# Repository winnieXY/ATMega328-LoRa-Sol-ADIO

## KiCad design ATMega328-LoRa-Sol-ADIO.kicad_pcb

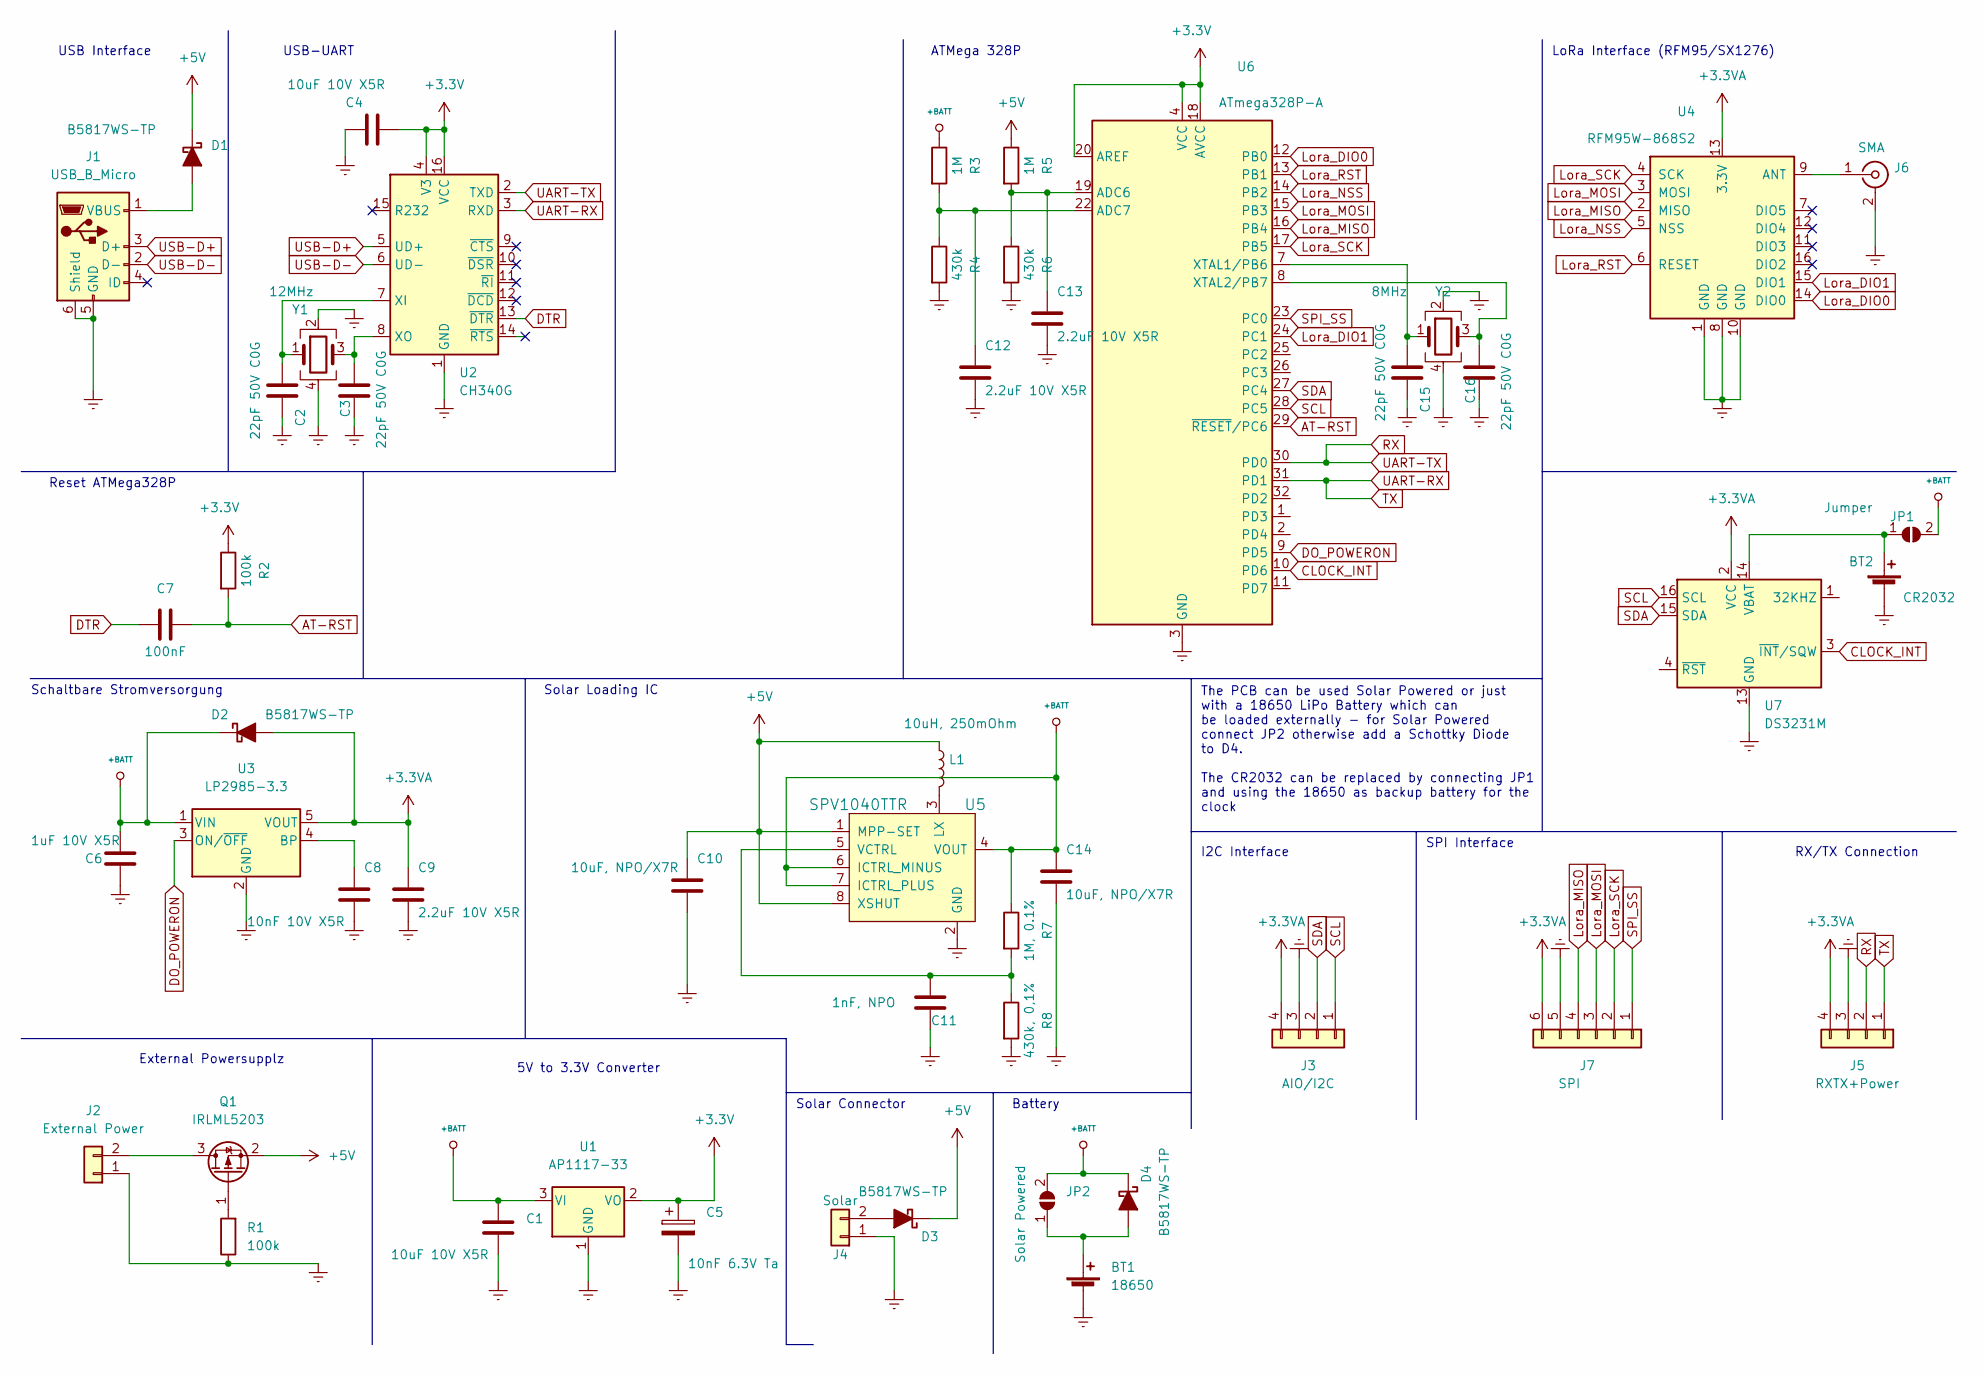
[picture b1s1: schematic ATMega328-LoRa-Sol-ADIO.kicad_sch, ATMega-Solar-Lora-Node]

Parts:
BT1: 18650; BatteryHolder_MPD_BH-18650-PC2
BT2: CR2032; Battery_Panasonic_CR2032-VS1N_Vertical_CircularHoles
C1, C4: 10uF 10V X5R; C_0603_1608Metric_Pad1.08x0.95mm_HandSolder; LCSC-Part C19702
C2, C3, C15, C16: 22pF 50V C0G; C_0603_1608Metric_Pad1.08x0.95mm_HandSolder; LCSC-Part C1653
C5: 10nF 6.3V Ta; CP_EIA-3528-15_AVX-H_Pad1.50x2.35mm_HandSolder; LCSC-Part C16133
C6: 1uF 10V X5R; C_0603_1608Metric_Pad1.08x0.95mm_HandSolder; LCSC-Part C19702
C7: 100nF; C_0603_1608Metric_Pad1.08x0.95mm_HandSolder; LCSC-Part C1653
C8: 10nF 10V X5R; C_0603_1608Metric_Pad1.08x0.95mm_HandSolder; LCSC-Part C19702
C9, C12, C13: 2.2uF 10V X5R; C_0603_1608Metric_Pad1.08x0.95mm_HandSolder; LCSC-Part C19702
C10, C14: 10uF, NPO/X7R; C_0603_1608Metric_Pad1.08x0.95mm_HandSolder; LCSC-Part C19702
C11: 1nF, NPO; C_0603_1608Metric_Pad1.08x0.95mm_HandSolder; LCSC-Part C19702
D1, D2, D3, D4: B5817WS-TP; D_SOD-323_HandSoldering; LCSC-Part C123899
J1: USB_B_Micro; USB_Micro-B_Molex-105017-0001
J2: External Power; JST_XH_B2B-XH-A_1x02_P2.50mm_Vertical
J3: AIO/I2C; JST_XH_B4B-XH-A_1x04_P2.50mm_Vertical
J4: Solar; JST_XH_B2B-XH-A_1x02_P2.50mm_Vertical
J5: RXTX+Power; JST_XH_B4B-XH-A_1x04_P2.50mm_Vertical
J6: SMA; SMA_Amphenol_901-144_Vertical
J7: SPI; JST_XH_B6B-XH-A_1x06_P2.50mm_Vertical
JP1: Jumper; SolderJumper-2_P1.3mm_Open_RoundedPad1.0x1.5mm
JP2: Solar Powered; SolderJumper-2_P1.3mm_Open_Pad1.0x1.5mm
L1: 10uH, 250mOhm; L_1206_3216Metric_Pad1.42x1.75mm_HandSolder
Q1: IRLML5203; SOT-23; LCSC-Part C2985623
R1: 100k; R_1206_3216Metric_Pad1.30x1.75mm_HandSolder; LCSC-Part C2907421
R2: 100k; R_1206_3216Metric_Pad1.30x1.75mm_HandSolder; LCSC-Part C17902
R3, R5: 1M; R_1206_3216Metric_Pad1.30x1.75mm_HandSolder; LCSC-Part C17902
R4, R6: 430k; R_1206_3216Metric_Pad1.30x1.75mm_HandSolder; LCSC-Part C17902
R7: 1M, 0.1%; R_1206_3216Metric_Pad1.30x1.75mm_HandSolder; LCSC-Part C17902
R8: 430k, 0,1%; R_1206_3216Metric_Pad1.30x1.75mm_HandSolder; LCSC-Part C17902
U1: AP1117-33; SOT-223-3_TabPin2; LCSC-Part C108785
U2: CH340G; SOIC-16_3.9x9.9mm_P1.27mm; LCSC-Part C14267
U3: LP2985-3.3; SOT-23-5
U4: RFM95W-868S2; HOPERF_RFM9XW_SMD; LCSC-Part C2844473
U5: SPV1040TTR; TSSOP-8_W4.4mm; MPN SPV1040TTR; Digi-Key_PN 497-11288-1-ND
U6: ATmega328P-A; TQFP-32_7x7mm_P0.8mm
U7: DS3231M; SOIC-16W_7.5x10.3mm_P1.27mm
Y1: 12MHz; Crystal_SMD_3225-4Pin_3.2x2.5mm_HandSoldering; LCSC-Part C9002
Y2: 8MHz; Crystal_SMD_3225-4Pin_3.2x2.5mm_HandSoldering; LCSC-Part C9002

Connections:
+3.3VA: C9.1, D2.2 (A), J3.4, J5.4, J7.6, U3.5 (VOUT), U4.13 (3.3V), U7.2 (VCC)
+3V3: C4.2, C5.1, R2.1, U1.2 (VO), U2.4 (V3), U2.16 (VCC), U6.4 (VCC), U6.6 (VCC), U6.18 (AVCC), U6.20 (AREF)
+5V: C10.1, D1.1 (K), D3.1 (K), L1.1, Q1.2 (S), R5.1, U5.1 (MPP-SET), U5.8 (XSHUT)
+BATT: C1.1, C6.1, C14.1, D2.1 (K), D4.1 (K), JP1.2 (B), JP2.2 (B), R3.1, R7.1, U1.3 (VI), U3.1 (VIN), U5.4 (VOUT), U5.6 (ICTRL_MINUS), U5.7 (ICTRL_PLUS)
AT-RST: C7.2, R2.2, U6.29 (~RESET/PC6)
CLOCK_INT: U6.10 (PD6), U7.3 (~INT/SQW)
DO_POWERON: U3.3 (ON/~OFF), U6.9 (PD5)
DTR: C7.1, U2.13 (~DTR)
Earth: BT1.2 (-), BT2.2 (-), C1.2, C2.2, C3.2, C4.1, C5.2, C6.2, C8.2, C9.2, C10.2, C11.2, C12.2, C13.2, C14.2, C15.2, C16.2, J1.5 (GND), J1.6 (Shield), J2.1, J3.3, J4.1, J5.3, J6.2 (Ext), J7.5, R1.1, R4.2, R6.2, R8.2, U1.1 (GND), U2.1 (GND), U3.2 (GND), U4.1 (GND), U4.8 (GND), U4.10 (GND), U5.2 (GND), U6.3 (GND), U6.5 (GND), U6.21 (GND), U7.5 (GND), U7.6 (GND), U7.7 (GND), U7.8 (GND), U7.9 (GND), U7.10 (GND), U7.11 (GND), U7.12 (GND), U7.13 (GND), Y1.2, Y1.4, Y2.2, Y2.4
Lora_DIO0: U4.14 (DIO0), U6.12 (PB0)
Lora_DIO1: U4.15 (DIO1), U6.24 (PC1)
Lora_MISO: J7.4, U4.2 (MISO), U6.16 (PB4)
Lora_MOSI: J7.3, U4.3 (MOSI), U6.15 (PB3)
Lora_NSS: U4.5 (NSS), U6.14 (PB2)
Lora_RST: U4.6 (RESET), U6.13 (PB1)
Lora_SCK: J7.2, U4.4 (SCK), U6.17 (PB5)
unnamed: BT1.1 (+), D4.2 (A), JP2.1 (A)
unnamed: BT2.1 (+), JP1.1 (A), U7.14 (VBAT)
unnamed: C2.1, U2.7 (XI), Y1.1
unnamed: C3.1, U2.8 (XO), Y1.3
unnamed: C8.1, U3.4 (BP)
unnamed: C11.1, R7.2, R8.1, U5.5 (VCTRL)
unnamed: C12.1, R3.2, R4.1, U6.22 (ADC7)
unnamed: C13.1, R5.2, R6.1, U6.19 (ADC6)
unnamed: C15.1, U6.7 (XTAL1/PB6), Y2.1
unnamed: C16.1, U6.8 (XTAL2/PB7), Y2.3
unnamed: D1.2 (A), J1.1 (VBUS)
unnamed: D3.2 (A), J4.2
unnamed: J2.2, Q1.3 (D)
unnamed: J6.1 (In), U4.9 (ANT)
unnamed: L1.2, U5.3 (LX)
unnamed: Q1.1 (G), R1.2
RX: J5.2, U2.2 (TXD), U6.30 (PD0)
SCL: J3.1, U6.28 (PC5), U7.16 (SCL)
SDA: J3.2, U6.27 (PC4), U7.15 (SDA)
SPI_SS: J7.1, U6.23 (PC0)
TX: J5.1, U2.3 (RXD), U6.31 (PD1)
USB-D+: J1.3 (D+), U2.5 (UD+)
USB-D-: J1.2 (D-), U2.6 (UD-)

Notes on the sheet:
USB-UART
The PCB can be used Solar Powered or just with a 18650 LiPo Battery which can be loaded externally - for Solar Powered connect JP2 otherwise add a Schottky Diode to D4. The CR2032 can be replaced by connecting JP1 and using the 18650 as backup battery for the clock
Battery
5V to 3.3V Converter
ATMega 328P
Reset ATMega328P
RX/TX Connection
Solar Loading IC
USB Interface
I2C Interface
Schaltbare Stromversorgung
LoRa Interface (RFM95/SX1276)
External Powersupplz
SPI Interface
Solar Connector

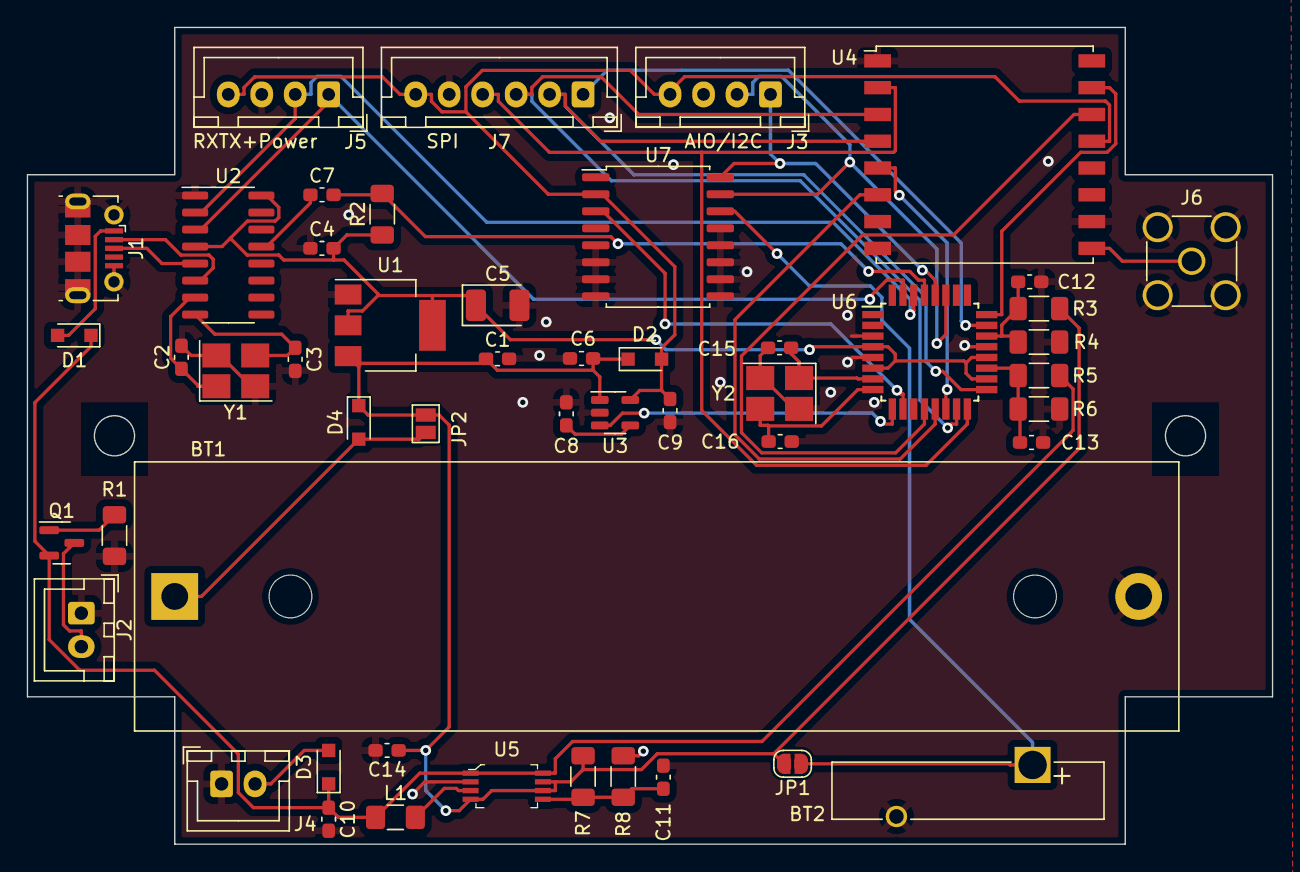
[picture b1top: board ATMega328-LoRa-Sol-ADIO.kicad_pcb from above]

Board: 2 copper layers, 93.0 x 61.0 mm, 50 parts (0 on the bottom side), 39 nets.

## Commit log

2022-07-07 Further work on the ATMega328 PCB
2022-07-08 Update the PCB Board and add nets to it
2022-08-16 First set of gerber files for production
2022-08-16 Cleanup
2022-08-16 Minor changes on PCB board due to GERBER file creation
2022-08-19 BOM List of the first PCB Board
